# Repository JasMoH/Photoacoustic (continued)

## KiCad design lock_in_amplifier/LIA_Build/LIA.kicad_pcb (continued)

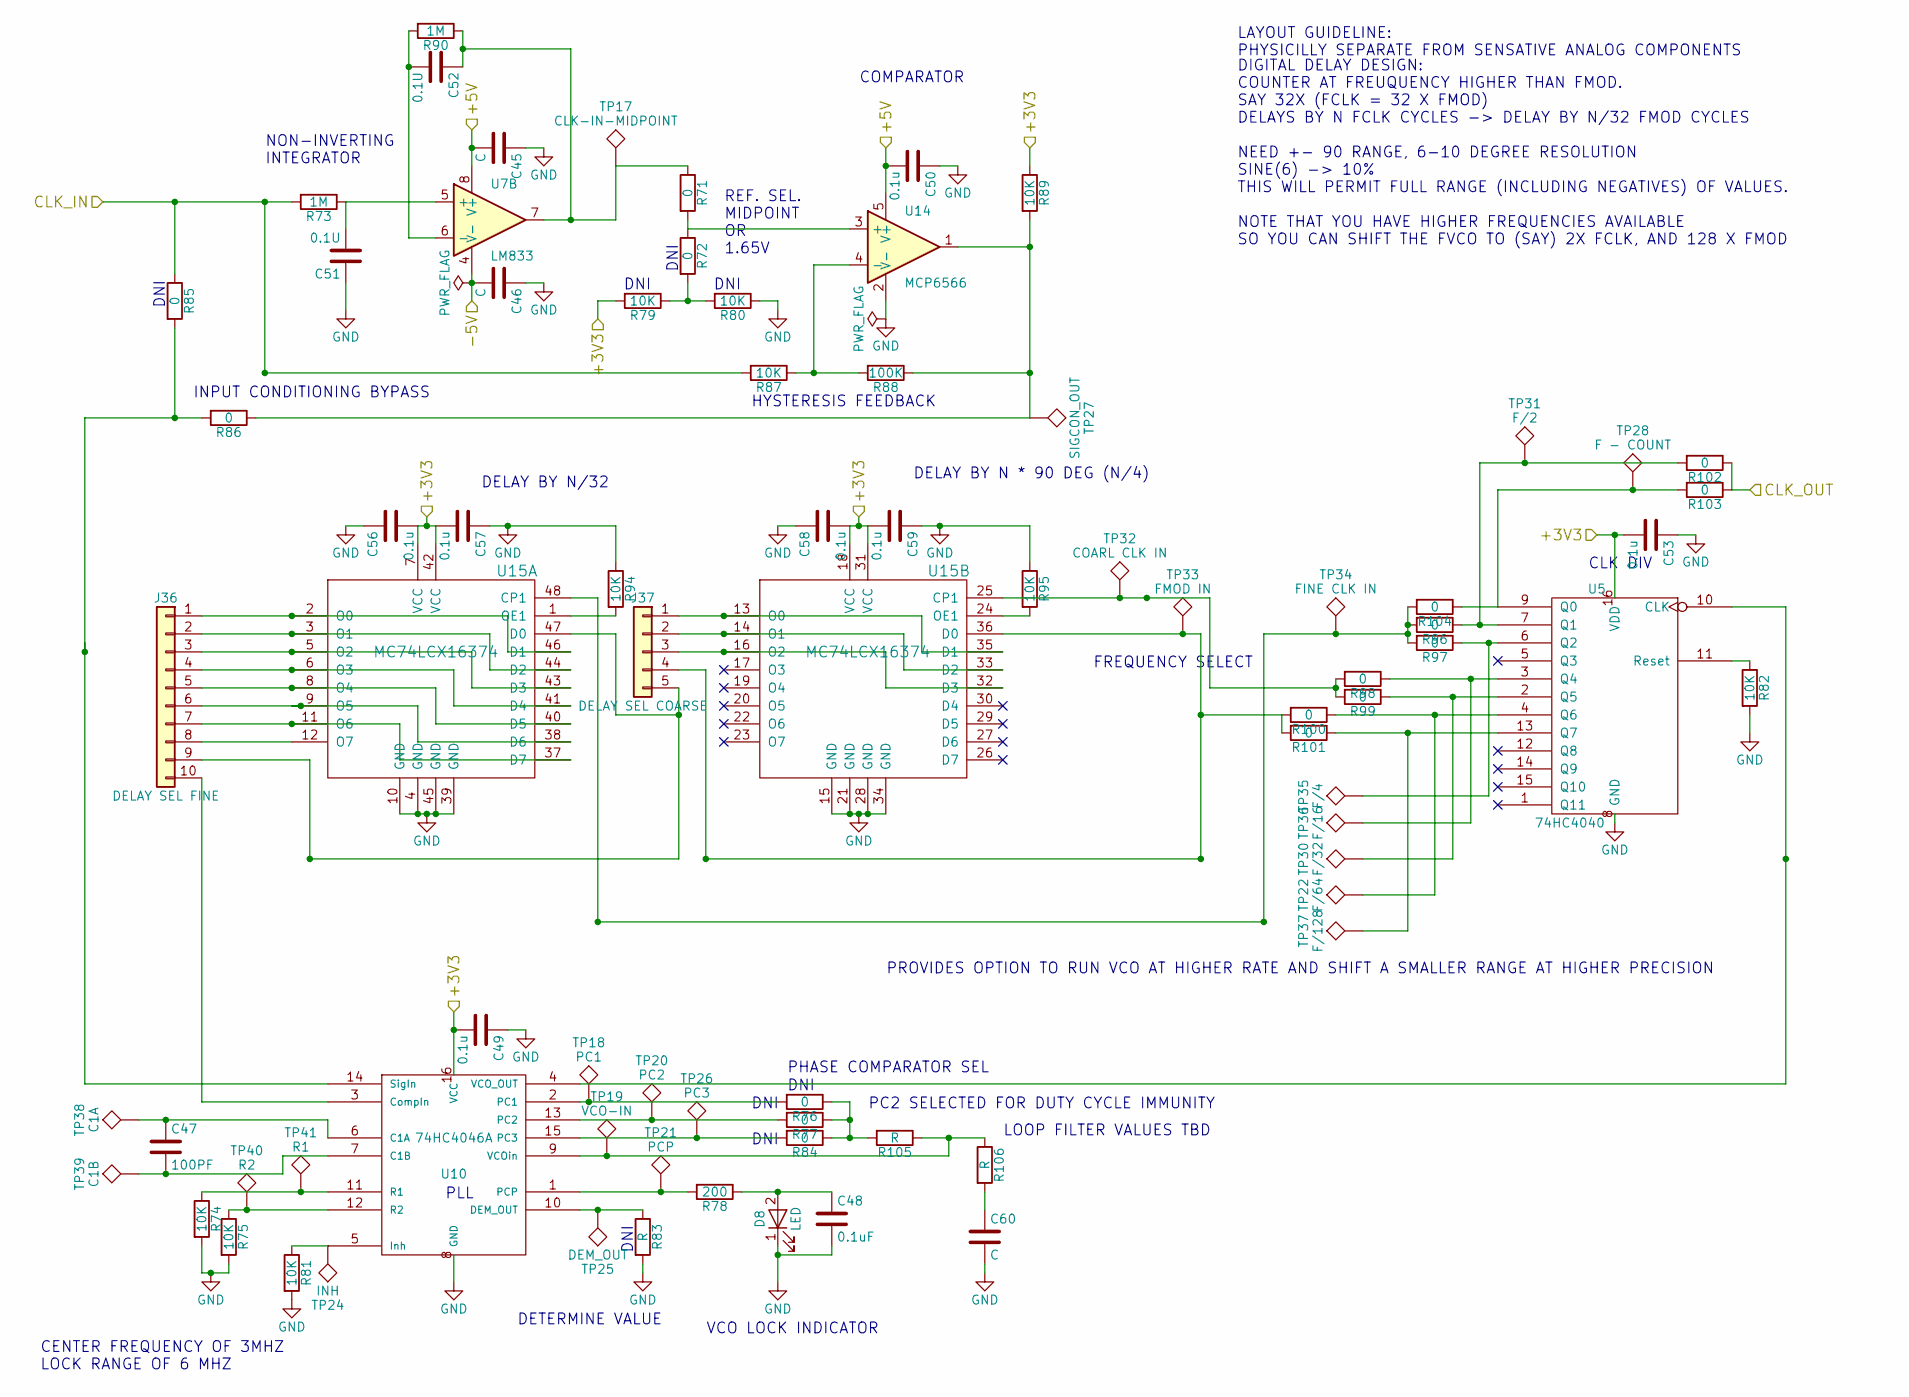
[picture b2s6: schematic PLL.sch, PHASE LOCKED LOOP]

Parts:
C45, C46, C60: C; C_0805
C47: 100PF; C_0805
C48: 0.1uF; C_0805
C49, C50, C53, C56, C57, C58, C59: 0.1u; C_0805
C51, C52: 0.1U; C_0805
D8: LED; LED_0805
J36: DELAY SEL FINE; Pin_Header_Straight_1x10_Pitch2.54mm
J37: DELAY SEL COARSE; Pin_Header_Straight_1x05_Pitch2.54mm
R71, R72, R76, R77, R84, R85, R86, R96, R97, R98, R99, R100, R101, R102, R103, R104: 0; R_0805
R73, R90: 1M; R_0805
R74, R75, R79, R80, R81, R82, R87, R89, R94, R95: 10K; R_0805
R78: 200; R_0805
R83, R105, R106: R; R_0805
R88: 100K; R_0805
TP17: CLK-IN-MIDPOINT; tyco_RCU_0603_Probe_Pad
TP18: PC1; tyco_RCU_0603_Probe_Pad
TP19: VCO-IN; tyco_RCU_0603_Probe_Pad
TP20: PC2; tyco_RCU_0603_Probe_Pad
TP21: PCP; tyco_RCU_0603_Probe_Pad
TP22: F/64; tyco_RCU_0603_Probe_Pad
TP24: INH; tyco_RCU_0603_Probe_Pad
TP25: DEM_OUT; tyco_RCU_0603_Probe_Pad
TP26: PC3; tyco_RCU_0603_Probe_Pad
TP27: SIGCON_OUT; tyco_RCU_0603_Probe_Pad
TP28: F - COUNT; tyco_RCU_0603_Probe_Pad
TP30: F/32; tyco_RCU_0603_Probe_Pad
TP31: F/2; tyco_RCU_0603_Probe_Pad
TP32: COARL CLK IN; tyco_RCU_0603_Probe_Pad
TP33: FMOD IN; tyco_RCU_0603_Probe_Pad
TP34: FINE CLK IN; tyco_RCU_0603_Probe_Pad
TP35: F/4; tyco_RCU_0603_Probe_Pad
TP36: F/16; tyco_RCU_0603_Probe_Pad
TP37: F/128; tyco_RCU_0603_Probe_Pad
TP38: C1A; tyco_RCU_0603_Probe_Pad
TP39: C1B; tyco_RCU_0603_Probe_Pad
TP40: R2; tyco_RCU_0603_Probe_Pad
TP41: R1; tyco_RCU_0603_Probe_Pad
U5: 74HC4040; TSSOP-16_4.4x5mm_Pitch0.65mm
U7: LM833; SO-8_5.3x6.2mm_Pitch1.27mm
U10: 74HC4046A; SOIC-16_3.9x9.9mm_Pitch1.27mm
U14: MCP6566; SOT-23-5
U15: MC74LCX16374; TSSOP-48_6.1x12.5mm_Pitch0.5mm

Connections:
+3V3: C49.2, C53.2, C56.2, C57.2, C58.2, C59.2, R79.2, R89.1, U5.16 (VDD), U10.16 (VCC), U15.7 (VCC), U15.18 (VCC), U15.31 (VCC), U15.42 (VCC); also elsewhere on the board
/PLL/CLK_IN: R73.2, R85.1, R87.2; also elsewhere on the board
/demodulator/CLK_IN: R102.1, R103.1; also elsewhere on the board
unnamed: C47.1, TP38.1, U10.6 (C1A)
unnamed: C47.2, TP39.1, U10.7 (C1B)
unnamed: C48.1, D8.2 (A), R78.1
unnamed: C51.2, R73.1, U7.5 (+)
unnamed: C52.1, R71.1, R90.1, TP17.1, U7.7
unnamed: C52.2, R90.2, U7.6 (-)
unnamed: C60.1, R106.2
unnamed: J36.1, U15.2 (O0), U15.46 (D1)
unnamed: J36.2, U15.3 (O1), U15.44 (D2)
unnamed: J36.3, U15.5 (O2), U15.43 (D3)
unnamed: J36.4, U15.6 (O3), U15.41 (D4)
unnamed: J36.5, U15.8 (O4), U15.40 (D5)
unnamed: J36.6, U15.9 (O5), U15.38 (D6)
unnamed: J36.7, U15.11 (O6), U15.37 (D7)
unnamed: J36.8, U15.12 (O7)
unnamed: J36.9, J37.5, U15.47 (D0)
unnamed: J36.10, U10.3 (CompIn)
unnamed: J37.1, U15.13 (O0), U15.35 (D1)
unnamed: J37.2, U15.14 (O1), U15.33 (D2)
unnamed: J37.3, U15.16 (O2), U15.32 (D3)
unnamed: J37.4, R100.2, R101.2, TP33.1, U15.36 (D0)
unnamed: R71.2, R72.1, U14.3 (+)
unnamed: R72.2, R79.1, R80.2
unnamed: R74.1, TP41.1, U10.11 (R1)
unnamed: R75.1, TP40.1, U10.12 (R2)
unnamed: R76.2, TP18.1, U10.2 (PC1)
unnamed: R77.2, TP20.1, U10.13 (PC2)
unnamed: R78.2, TP21.1, U10.1 (PCP)
unnamed: R81.1, TP24.1, U10.5 (Inh)
unnamed: R82.1, U5.11 (Reset)
unnamed: R83.1, TP25.1, U10.10 (DEM_OUT)
unnamed: R84.2, TP26.1, U10.15 (PC3)
unnamed: R85.2, R86.2, U10.14 (SigIn)
unnamed: R86.1, R88.1, R89.2, TP27.1, U14.1
unnamed: R87.1, R88.2, U14.4 (-)
unnamed: R94.2, U15.1 (OE1)
unnamed: R95.2, U15.24 (OE1)
unnamed: R97.1, TP35.1, U5.6 (Q2)
unnamed: R98.1, TP36.1, U5.3 (Q4)
unnamed: R98.2, R99.2, TP32.1, U15.25 (CP1)
unnamed: R99.1, TP30.1, U5.2 (Q5)
unnamed: R100.1, TP22.1, U5.4 (Q6)
unnamed: R101.1, TP37.1, U5.13 (Q7)
unnamed: R96.1, R102.2, TP31.1, U5.7 (Q1)
unnamed: R103.2, R104.1, TP28.1, U5.9 (Q0)
unnamed: R96.2, R97.2, R104.2, TP34.1, U15.48 (CP1)
unnamed: R105.1, R106.1, TP19.1, U10.9 (VCOin)
unnamed: R76.1, R77.1, R84.1, R105.2
unnamed: U5.10 (CLK), U10.4 (VCO_OUT)

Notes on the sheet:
PLL
CLK DIV
LAYOUT GUIDELINE: PHYSICILLY SEPARATE FROM SENSATIVE ANALOG COMPONENTS
NON-INVERTING INTEGRATOR
COMPARATOR
REF. SEL. MIDPOINT OR 1.65V
FREQUENCY SELECT
DNI
PHASE COMPARATOR SEL
VCO LOCK INDICATOR
DETERMINE VALUE
INPUT CONDITIONING BYPASS
HYSTERESIS FEEDBACK
DIGITAL DELAY DESIGN: COUNTER AT FREUQUENCY HIGHER THAN FMOD. SAY 32X (FCLK = 32 X FMOD) DELAYS BY N FCLK CYCLES -> DELAY BY N/32 FMOD CYCLES NEED +- 90 RANGE, 6-10 DEGREE RESOLUTION SINE(6) -> 10% THIS WILL PERMIT FULL RANGE (INCLUDING NEGATIVES) OF VALUES. NOTE THAT YOU HAVE HIGHER FREQUENCIES AV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
DELAY BY N * 90 DEG (N/4)
DELAY BY N/32
PROVIDES OPTION TO RUN VCO AT HIGHER RATE AND SHIFT A SMALLER RANGE AT HIGHER PRECISION
CENTER FREQUENCY OF 3MHZ LOCK RANGE OF 6 MHZ
PC2 SELECTED FOR DUTY CYCLE IMMUNITY
LOOP FILTER VALUES TBD

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
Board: 2 copper layers, 295 parts (26 on the bottom side), 156 nets, no tracks yet.

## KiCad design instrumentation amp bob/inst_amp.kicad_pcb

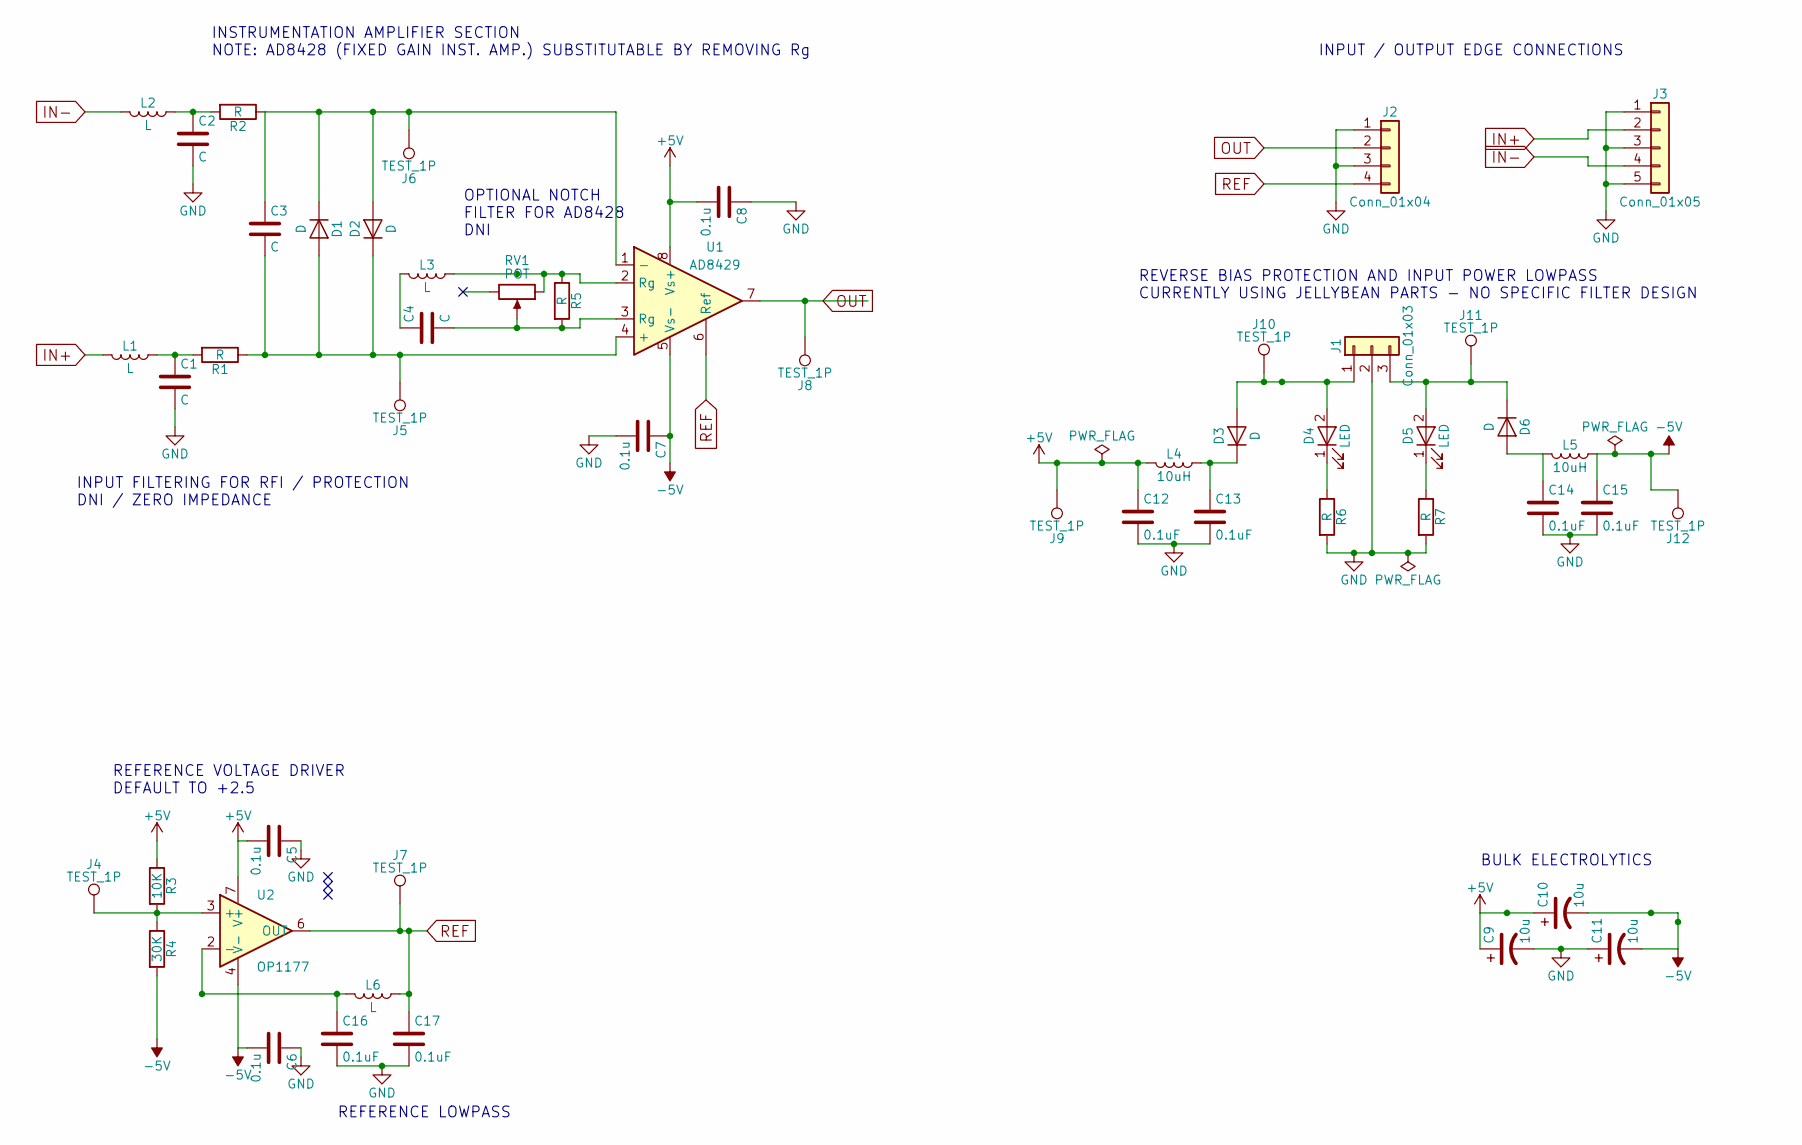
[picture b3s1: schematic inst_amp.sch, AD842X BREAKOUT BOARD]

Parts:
C1, C2, C3, C4: C; C_0805_HandSoldering
C5, C6, C7, C8: 0.1u; C_0805_HandSoldering
C9, C10, C11: 10u; CP_Elec_6.3x7.7
C12, C13, C14, C15, C16, C17: 0.1uF; C_0805_HandSoldering
D1, D2, D3, D6: D; D_0805
D4, D5: LED; D_0805
J1: Conn_01x03; Pin_Header_Angled_1x03_Pitch2.54mm
J2: Conn_01x04; Pin_Header_Angled_1x04_Pitch2.54mm
J3: Conn_01x05; Pin_Header_Angled_1x05_Pitch2.54mm
J4, J5, J6, J7, J8, J9, J10, J11, J12: TEST_1P; Measurement_Point_Round-SMD-Pad_Big
L1, L2, L3, L6: L; L_0805_HandSoldering
L4, L5: 10uH; L_0805_HandSoldering
R1, R2, R5, R6, R7: R; R_0805_HandSoldering
R3: 10K; R_0805_HandSoldering
R4: 30K; R_0805_HandSoldering
RV1: POT; Potentiometer_Trimmer_Bourns_PV36W
U1: AD8429; SOIC-8_3.9x4.9mm_Pitch1.27mm
U2: OP1177; MSOP-8-1EP_3x3mm_Pitch0.65mm

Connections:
+5V: C5.2, C8.2, C9.1, C10.1, C12.1, J9.1, L4.2, R3.1, U1.8 (Vs+), U2.7 (V+)
-5V: C6.2, C7.1, C10.2, C11.2, C15.1, J12.1, L5.1, R4.2, U1.5 (Vs-), U2.4 (V-)
GND: C1.2, C2.2, C5.1, C6.1, C7.2, C8.1, C9.2, C11.1, C12.2, C13.2, C14.2, C15.2, C16.2, C17.2, J1.2, J2.1, J2.3, J3.1, J3.3, J3.5, R6.2, R7.2
IN+: J3.2, L1.2
IN-: J3.4, L2.2
unnamed: C1.1, L1.1, R1.2
unnamed: C2.1, L2.1, R2.2
unnamed: C3.1, D1.1 (K), D2.2 (A), J6.1, R2.1, U1.1 (-)
unnamed: C3.2, D1.2 (A), D2.1 (K), J5.1, R1.1, U1.4 (+)
unnamed: C4.1, L3.2
unnamed: C4.2, R5.2, RV1.2, U1.3 (Rg)
unnamed: C13.1, D3.1 (K), L4.1
unnamed: C14.1, D6.2 (A), L5.2
unnamed: C16.1, L6.2, U2.2 (-)
unnamed: D3.2 (A), D4.2 (A), J1.1, J10.1
unnamed: D4.1 (K), R6.1
unnamed: D5.1 (K), R7.1
unnamed: D5.2 (A), D6.1 (K), J1.3, J11.1
unnamed: J4.1, R3.2, R4.1, U2.3 (+)
unnamed: L3.1, R5.1, RV1.1, U1.2 (Rg)
OUT: J2.2, J8.1, U1.7
REF: C17.1, J2.4, J7.1, L6.1, U1.6 (Ref), U2.6 (OUT)

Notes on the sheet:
REFERENCE VOLTAGE DRIVER DEFAULT TO +2.5
OPTIONAL NOTCH FILTER FOR AD8428 DNI
INPUT FILTERING FOR RFI / PROTECTION DNI / ZERO IMPEDANCE
INSTRUMENTATION AMPLIFIER SECTION NOTE: AD8428 (FIXED GAIN INST. AMP.) SUBSTITUTABLE BY REMOVING Rg
INPUT / OUTPUT EDGE CONNECTIONS
BULK ELECTROLYTICS
REVERSE BIAS PROTECTION AND INPUT POWER LOWPASS CURRENTLY USING JELLYBEAN PARTS - NO SPECIFIC FILTER DESIGN
REFERENCE LOWPASS

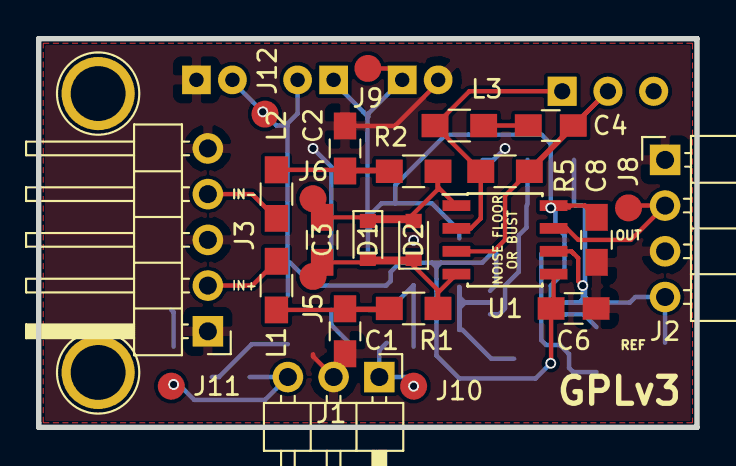
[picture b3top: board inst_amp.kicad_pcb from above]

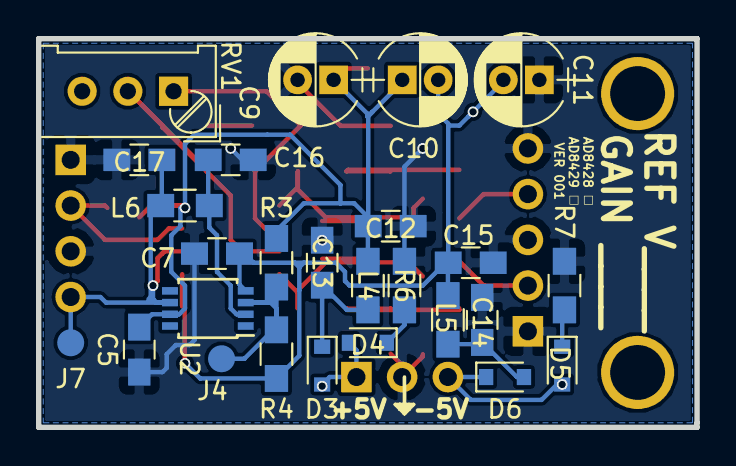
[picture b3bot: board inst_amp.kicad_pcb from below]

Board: 2 copper layers, 36.6 x 21.6 mm, 51 parts (26 on the bottom side), 22 nets.

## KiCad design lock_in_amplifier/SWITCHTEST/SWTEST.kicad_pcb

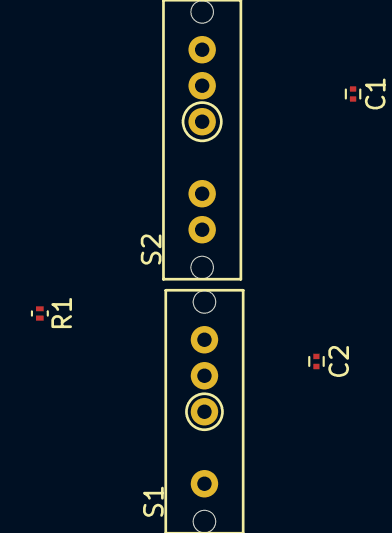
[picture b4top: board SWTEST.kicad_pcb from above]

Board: 2 copper layers, 5 parts (0 on the bottom side), 6 nets, no tracks yet.

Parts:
C1, C2: C; C_0201
R1: R; R_0201
S1: SP3T; SP3T_CK_SS-14D0839-VG
S2: SP4T; SP4T_C&K_SS-14D0839-VG

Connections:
unnamed: C1.1, S2.3, S2.4
unnamed: C1.2, S2.1, S2.2
unnamed: C2.1, S1.2, S1.3
unnamed: C2.2, S1.1
unnamed: R1.1, S2.C
unnamed: R1.2, S1.C

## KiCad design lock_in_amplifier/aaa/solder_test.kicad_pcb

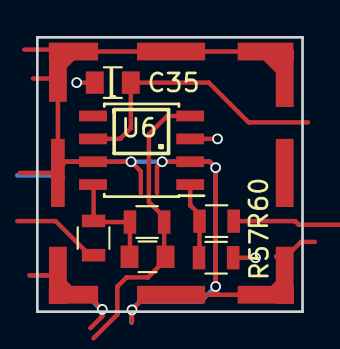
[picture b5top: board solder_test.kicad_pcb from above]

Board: 2 copper layers, 14.7 x 15.2 mm, 8 parts (0 on the bottom side), 6 nets.

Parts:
C35: 0.1u; C_0805
C36: 10pF; C_0805
J17: RF_Shield_One_Piece; SMS-201
R55: 100M; R_0805
R57: 0; R_0805
R60: 10K; R_0805
R64: 100; R_0805
U6: lmp7721; SOIC-8_3.9x4.9mm_Pitch1.27mm

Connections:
/sheet5A330123/GUARD: J17.1, U6.2, U6.7
GND: C35.1, R57.1, U6.3
unnamed: C35.2, U6.6
unnamed: C36.1, R55.1, U6.4
unnamed: C36.2, R55.2, R64.1, U6.8
unnamed: R57.2, R60.2, U6.1

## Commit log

2017-10-26 Add initial board for instrumentation amplifier
2017-10-27 incorporated schematic changes from peer review
    power PI filter
    test points
    reference voltage conector
    reference voltage LP filter
    power reverse bias protection
    power presense led
2017-10-27 selected pot footprint, fixed pot connection bug
2017-10-27 incorporated review comments to layout
2017-11-27 started creating final lock in amplifier
2017-11-29 power supply, amp chain first pass
2017-12-01 initial transimpedance selection, lna refinement
    amp overload led
    switch comps added
2017-12-01 TIA, switch trades
2017-12-04 switch footprints, lm833 usage, pll investigation
2017-12-06 PLL initial implementation
2017-12-06 Added quadrature demod, phase shift to pll
2017-12-06 pll finalized - misc cleanup - review candidate
2017-12-07 pdf for design review
2017-12-11 initial layout of pll test board
2017-12-14 manufacturing test for PLL
2017-12-15 started LNA test board.
2017-12-15 initial lna and power floorplan finished.
2017-12-18 initial LNA test layout
    everything connected - moving towards a manufacturability test.
2017-12-18 correct lmp7721 package - soic
2017-12-18 finished relayout of tia - soic
2017-12-19 silkscreen readability changes
2017-12-29 soldering manufacturing check
2018-01-04 adressing comments - fets
2018-01-04 misc debug
2018-01-04 misc updates
2018-01-04 added sheets
2018-01-10 changed pin to static const
